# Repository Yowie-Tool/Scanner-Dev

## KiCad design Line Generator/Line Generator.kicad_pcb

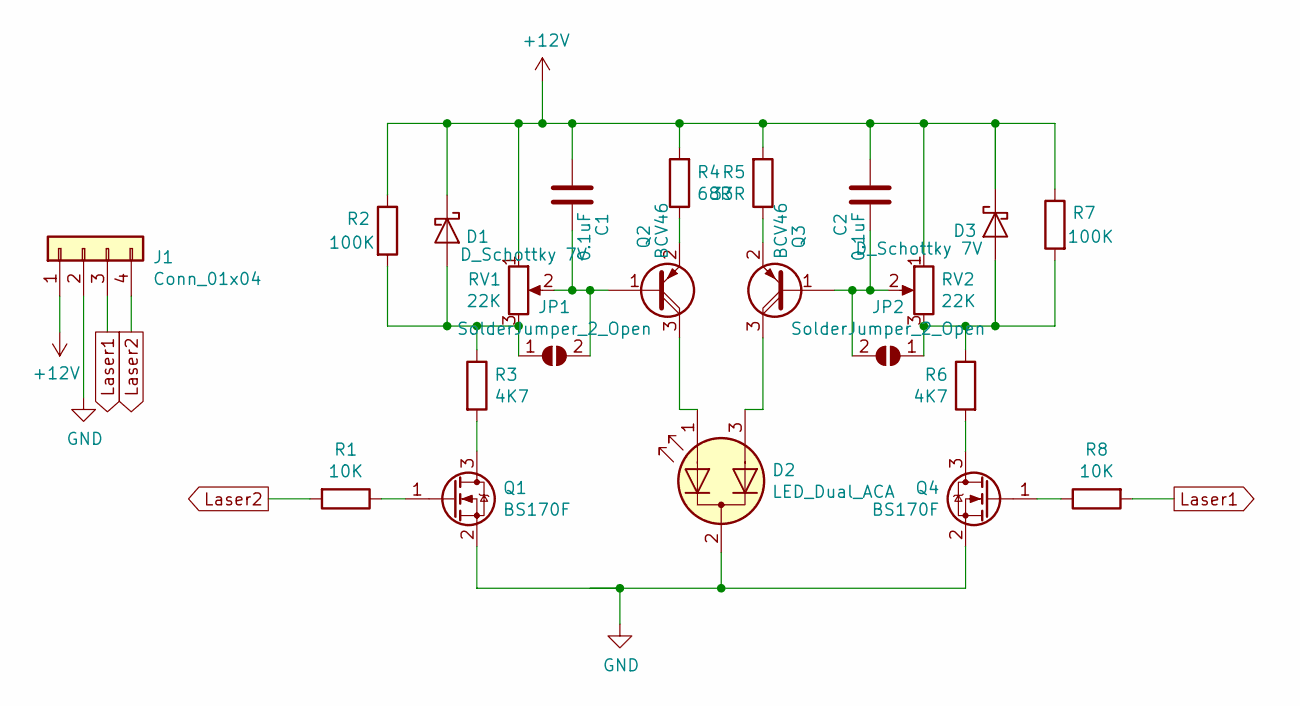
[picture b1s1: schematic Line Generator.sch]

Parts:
C1, C2: 0.1uF; C_0805_2012Metric_Pad1.15x1.40mm_HandSolder
D1, D3: D_Schottky 7V; D_SOD-323_HandSoldering
D2: LED_Dual_ACA; PinSocket_1x03_P1.27mm_Vertical
J1: Conn_01x04; JST_PH_B4B-PH-SM4-TB_1x04-1MP_P2.00mm_Vertical
JP1, JP2: SolderJumper_2_Open; SolderJumper-2_P1.3mm_Open_RoundedPad1.0x1.5mm
Q1, Q4: BS170F; SOT-23
Q2, Q3: BCV46; SOT-23-3
R1, R8: 10K; R_0805_2012Metric_Pad1.15x1.40mm_HandSolder
R2, R7: 100K; R_0805_2012Metric_Pad1.15x1.40mm_HandSolder
R3, R6: 4K7; R_0805_2012Metric_Pad1.15x1.40mm_HandSolder
R4: 68R; R_0805_2012Metric_Pad1.15x1.40mm_HandSolder
R5: 33R; R_0805_2012Metric_Pad1.15x1.40mm_HandSolder
RV1, RV2: 22K; Potentiometer_Bourns_3006P_Horizontal

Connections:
+12V: C1.2, C2.2, D1.1 (K), D3.1 (K), J1.1, R2.1, R4.2, R5.2, R7.1, RV1.1, RV2.1
GND: D2.2 (K), J1.2, Q1.2 (S), Q4.2 (S)
Laser1: J1.3, R8.2
Laser2: J1.4, R1.2
unnamed: C1.1, JP1.2 (B), Q2.1 (B), RV1.2
unnamed: C2.1, JP2.2 (B), Q3.1 (B), RV2.2
unnamed: D1.2 (A), JP1.1 (A), R2.2, R3.1, RV1.3
unnamed: D2.1 (A1), Q2.3 (C)
unnamed: D2.3 (A2), Q3.3 (C)
unnamed: D3.2 (A), JP2.1 (A), R6.1, R7.2, RV2.3
unnamed: Q1.1 (G), R1.1
unnamed: Q1.3 (D), R3.2
unnamed: Q2.2 (E), R4.1
unnamed: Q3.2 (E), R5.1
unnamed: Q4.1 (G), R8.1
unnamed: Q4.3 (D), R6.2

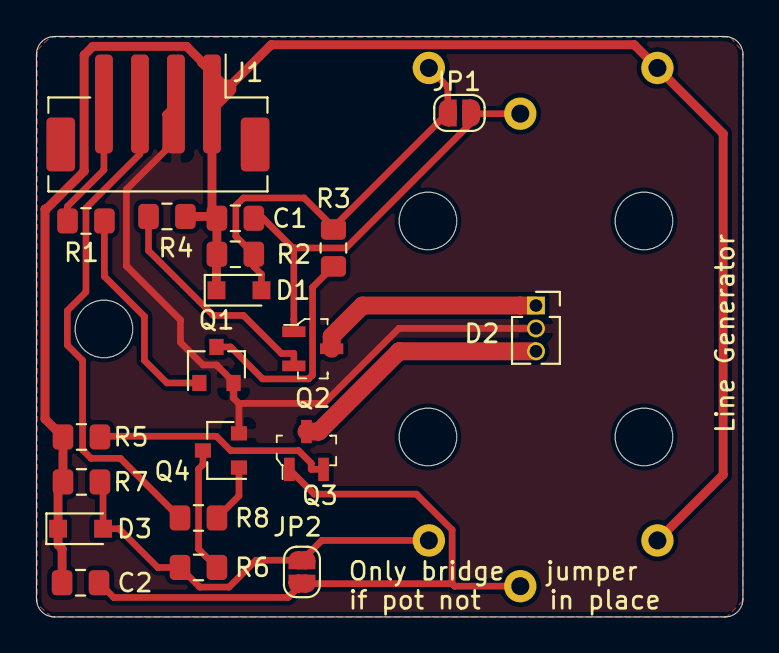
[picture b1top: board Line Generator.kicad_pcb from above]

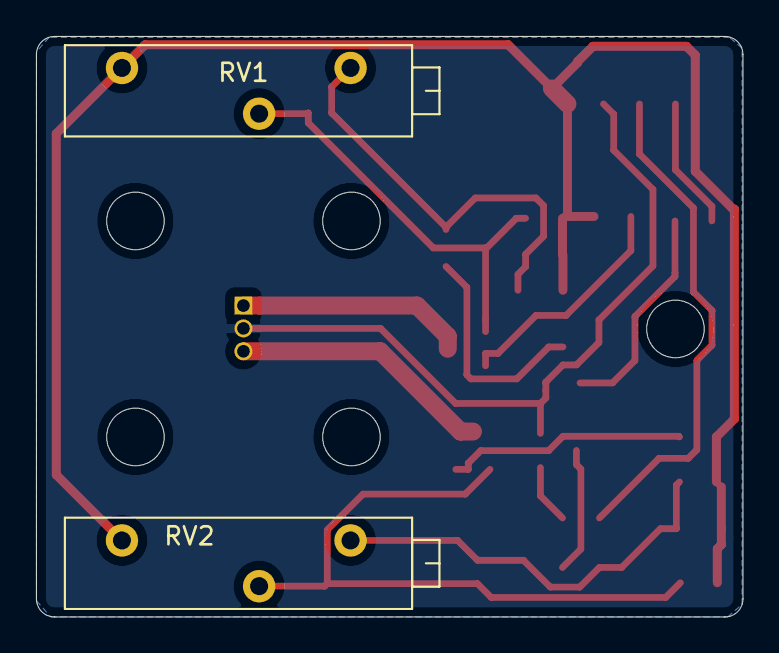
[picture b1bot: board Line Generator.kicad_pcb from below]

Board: 2 copper layers, 39.2 x 32.2 mm, 27 parts (2 on the bottom side), 16 nets.

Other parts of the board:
Mount1, Mount2, Mount3, Mount4, Mount5: MountingHole_3.2mm_M3_ISO7380
